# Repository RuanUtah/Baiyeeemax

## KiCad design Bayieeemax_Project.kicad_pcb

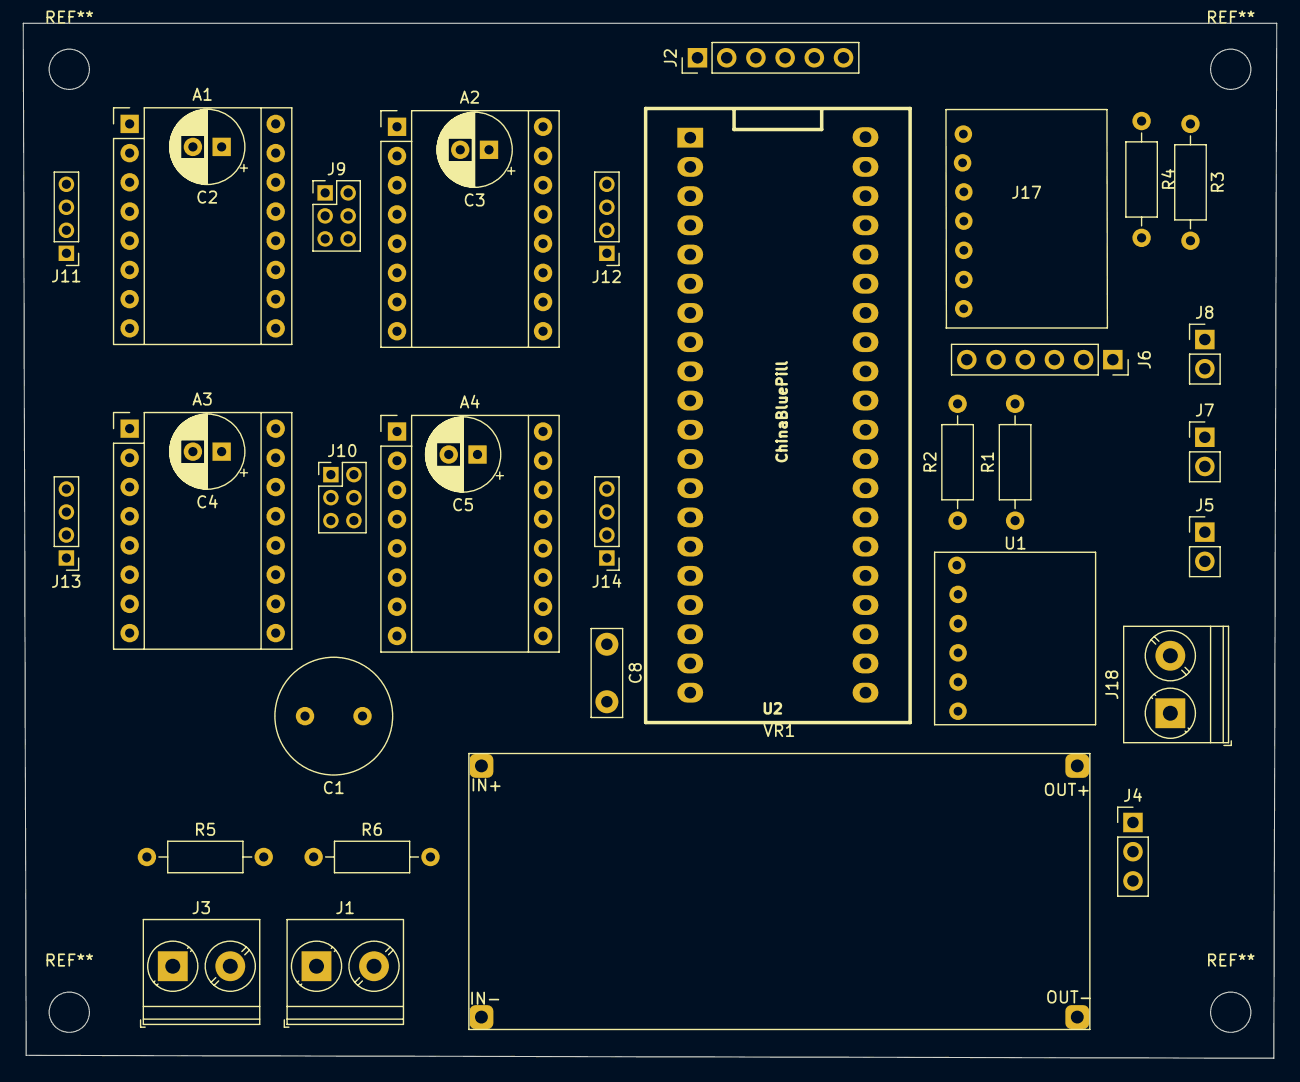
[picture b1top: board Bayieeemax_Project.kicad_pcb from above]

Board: 2 copper layers, 109.0 x 90.0 mm, 35 parts (0 on the bottom side), 45 nets, no tracks yet.

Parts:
A1: Pololu_Breakout_DRV8825_1; Pololu_Breakout-16_15.2x20.3mm
A2: Pololu_Breakout_DRV8825_2; Pololu_Breakout-16_15.2x20.3mm
A3: Pololu_Breakout_DRV8825_3; Pololu_Breakout-16_15.2x20.3mm
A4: Pololu_Breakout_DRV8825_4; Pololu_Breakout-16_15.2x20.3mm
C1: 1000uF; C_Radial_D10.0mm_H12.5mm_P5.00mm
C2, C3, C4, C5: 100uF; CP_Radial_D6.3mm_P2.50mm
C8: 100nf; C_Disc_D7.5mm_W2.5mm_P5.00mm
J1: Baterry_P.IN; TerminalBlock_Phoenix_PT-1,5-2-5.0-H_1x02_P5.00mm_Horizontal
J2: USB_TTL; PinHeader_1x06_P2.54mm_Vertical
J3: Current_power_in; TerminalBlock_Phoenix_PT-1,5-2-5.0-H_1x02_P5.00mm_Horizontal
J4: ACS_SENSOR; PinHeader_1x03_P2.54mm_Vertical
J5: I2C_MPU_Raspberry; PinHeader_1x02_P2.54mm_Vertical
J6: GPS_Conn; PinSocket_1x06_P2.54mm_Vertical
J7: TTL_Raspberry; PinHeader_1x02_P2.54mm_Vertical
J8: I2C_MAX30100_Raspberry; PinHeader_1x02_P2.54mm_Vertical
J9: MicroStep_1/16_wheels; PinHeader_2x03_P2.00mm_Vertical
J10: MicroStep_1/32_wheels; PinHeader_2x03_P2.00mm_Vertical
J11: Motor1; PinHeader_1x04_P2.00mm_Vertical
J12: Motor2; PinHeader_1x04_P2.00mm_Vertical
J13: Motor3; PinHeader_1x04_P2.00mm_Vertical
J14: Motor4; PinHeader_1x04_P2.00mm_Vertical
J17: i2C_MAX30100; MAX30100
J18: Raspberry_POWER_IN; TerminalBlock_Phoenix_PT-1,5-2-5.0-H_1x02_P5.00mm_Horizontal
R1: 1.7K; R_Axial_DIN0207_L6.3mm_D2.5mm_P10.16mm_Horizontal
R2: 3.3K; R_Axial_DIN0207_L6.3mm_D2.5mm_P10.16mm_Horizontal
R3, R4: 10K; R_Axial_DIN0207_L6.3mm_D2.5mm_P10.16mm_Horizontal
R5: 13K; R_Axial_DIN0207_L6.3mm_D2.5mm_P10.16mm_Horizontal
R6: 3K; R_Axial_DIN0207_L6.3mm_D2.5mm_P10.16mm_Horizontal
U1: MPU-9250
U2: ChinaBluePill; BluePill_STM32F103C
VR1: XL4015; DCDC_stepdown_75W-XL4015

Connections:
+3V3: J6.5, J17.1, R3.1, R4.1, U1.13, U2.20, U2.38
+5V: A1.13, A1.14, A2.13, A2.14, A3.13, A3.14, A4.13, A4.14, C8.1, J2.1, J4.1, J9.6, J10.2, J10.4, J10.6, J18.1, U2.18
+12V: C1.2, J3.1, R5.1
+15V: A1.8, A2.8, A3.8, A4.8, C2.1, C3.1, C4.1, C5.1
/ACS: R1.2, R2.1, U2.30
/AVS: R5.2, R6.1, U2.31
/DIREC_1: A1.16, U2.8
/DIREC_2: A2.16, U2.9
/DIREC_3: A3.16, U2.10
/DIREC_4: A4.16, U2.1
/M0: A1.10, A2.10, A3.10, A4.10, J9.1, J10.1
/M1: A1.11, A2.11, A3.11, A4.11, J9.3, J10.3
/M2: A1.12, A2.12, A3.12, A4.12, J9.5, J10.5
/MOTOR1_A1: A1.4, J11.3
/MOTOR1_A2: A1.3, J11.4
/MOTOR1_B1: A1.5, J11.2
/MOTOR1_B2: A1.6, J11.1
/MOTOR2_A1: A2.4, J12.3
/MOTOR2_A2: A2.3, J12.4
/MOTOR2_B1: A2.5, J12.2
/MOTOR2_B2: A2.6, J12.1
/MOTOR3_A1: A3.4, J13.3
/MOTOR3_A2: A3.3, J13.4
/MOTOR3_B1: A3.5, J13.2
/MOTOR3_B2: A3.6, J13.1
/MOTOR4_A1: A4.4, J14.3
/MOTOR4_A2: A4.3, J14.4
/MOTOR4_B1: A4.5, J14.2
/MOTOR4_B2: A4.6, J14.1
/RX_GPS: J6.3, J7.1, U2.28
/Rx_SERIAL: J2.5, U2.36
/SCL_MAX3100: J8.1, J17.2, R3.2, U2.16
/SDA_MAX3100: J8.2, J17.3, R4.2, U2.17
/SDA_MPU9250: J5.2, U1.24, U2.15
/SLC_MPU9250: J5.1, U1.23, U2.14
/STEP_1: A1.15, U2.32
/STEP_2: A2.15, U2.5
/STEP_3: A3.15, U2.6
/STEP_4: A4.15, U2.7
/TX_GPS: J6.4, J7.2, U2.27
/Tx_SERIAL: J2.4, U2.35
/~INT_MAX3100: J17.4, U2.13
GND: A1.1, A1.7, A2.1, A2.7, A3.1, A3.7, A4.1, A4.7, C1.1, C2.2, C3.2, C4.2, C5.2, C8.2, J1.2, J2.6, J4.3, J9.2, J9.4, J18.2, R2.2, R6.2, U1.18, U2.19, U2.39, U2.40, VR1.1
unnamed: J1.1, J3.2
unnamed: J4.2, R1.1

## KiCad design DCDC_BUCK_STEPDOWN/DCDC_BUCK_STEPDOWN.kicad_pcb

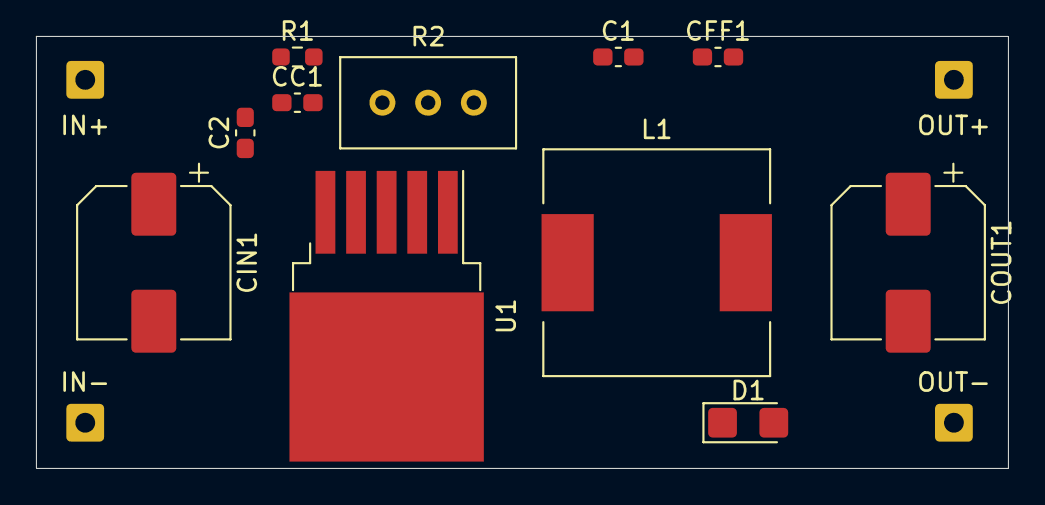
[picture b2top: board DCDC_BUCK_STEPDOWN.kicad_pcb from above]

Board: 2 copper layers, 54.0 x 24.0 mm, 15 parts (0 on the bottom side), 7 nets, no tracks yet.

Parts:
C1, C2: 105; C_0603_1608Metric_Pad1.08x0.95mm_HandSolder
CC1: 105; C_0603_1608Metric_Pad1.08x0.95mm_HandSolder
CFF1: 33nF; C_0603_1608Metric_Pad1.08x0.95mm_HandSolder
CIN1: 220uF; CP_Elec_8x10
COUT1: 330uF; CP_Elec_8x10
D1: MBRD1045G; D_1206_3216Metric_Castellated
IN+: Conn_01x01_Female; SolderWire-0.5sqmm_1x01_D0.9mm_OD2.1mm
IN-: Conn_01x01_Female; SolderWire-0.5sqmm_1x01_D0.9mm_OD2.1mm
L1: 47uH; L_12x12mm_H8mm
OUT+: Conn_01x01_Female; SolderWire-0.5sqmm_1x01_D0.9mm_OD2.1mm
OUT-: Conn_01x01_Female; SolderWire-0.5sqmm_1x01_D0.9mm_OD2.1mm
R1: 3.3K; R_0603_1608Metric_Pad0.98x0.95mm_HandSolder
R2: 10K; Potentiometer_Bourns_3296W_Vertical
U1: LM2575-3.3BU; TO-263-5_TabPin3

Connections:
GND: C1.2, C2.2, CIN1.2, COUT1.2, D1.2, IN-.1, OUT-.1, R1.2, U1.3
unnamed: C1.1, CC1.1, CIN1.1, IN+.1, U1.1
unnamed: C2.1, CFF1.1, COUT1.1, L1.2, OUT+.1, R2.1
unnamed: CC1.2, U1.5
unnamed: CFF1.2, U1.2
unnamed: D1.1, L1.1, U1.4
unnamed: R1.1, R2.2

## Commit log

2021-11-17 Baiyeeemax kicad files
2021-11-22 Bayieeemax new libraries and componentes
2021-12-02 new symbols
2021-12-09 Novas alterações
2021-12-20 edicoes
2021-12-24 eeschema edicoes
2021-12-27 V01 do circuito
2022-02-18 New files
2022-04-17 Board
